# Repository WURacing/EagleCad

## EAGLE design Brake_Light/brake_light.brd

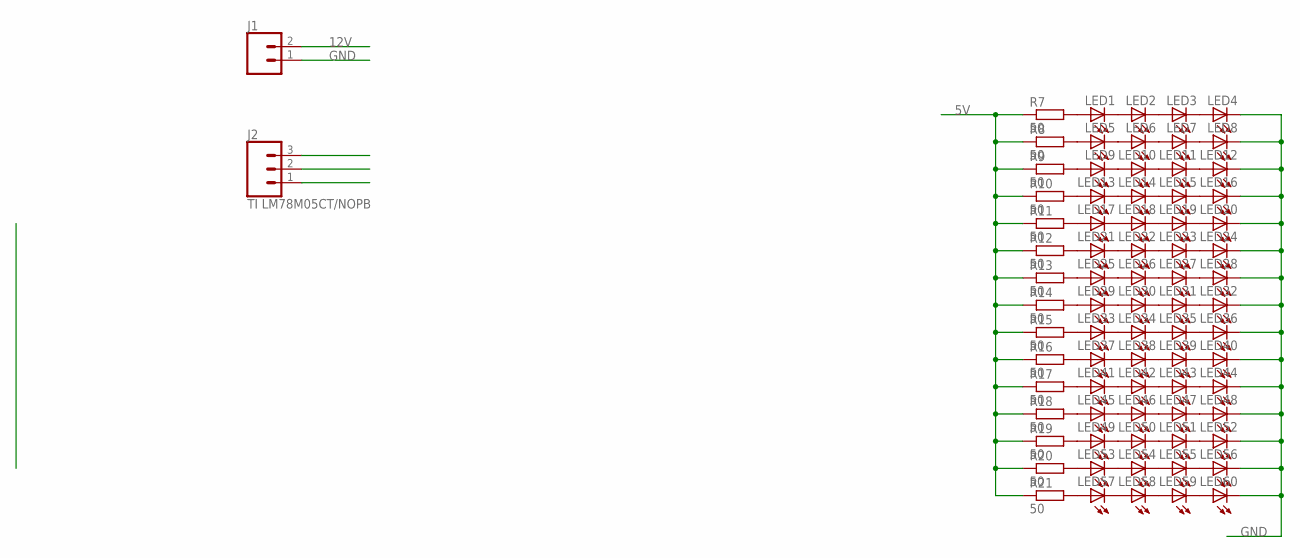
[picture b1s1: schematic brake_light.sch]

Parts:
J1: CONN_02; 1X02
J2: TI LM78M05CT/NOPB; 1X03
LED1, LED2, LED3, LED4, LED5, LED6, LED7, LED8, LED9, LED10, LED11, LED12, LED13, LED14, LED15, LED16, LED17, LED18, LED19, LED20, LED21, LED22, LED23, LED24, LED25, LED26, LED27, LED28, LED29, LED30, LED31, LED32, LED33, LED34, LED35, LED36, LED37, LED38, LED39, LED40, LED41, LED42, LED43, LED44, LED45, LED46, LED47, LED48, LED49, LED50, LED51, LED52, LED53, LED54, LED55, LED56, LED57, LED58, LED59, LED60: LED5MM
R7, R8, R9, R10, R11, R12, R13, R14, R15, R16, R17, R18, R19, R20, R21: 50; R1206

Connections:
5V: J2.3, R7.1, R8.1, R9.1, R10.1, R11.1, R12.1, R13.1, R14.1, R15.1, R16.1, R17.1, R18.1, R19.1, R20.1, R21.1
12V: J1.2, J2.1
GND: J1.1, J2.2, LED4.K (C), LED8.K (C), LED12.K (C), LED16.K (C), LED20.K (C), LED24.K (C), LED28.K (C), LED32.K (C), LED36.K (C), LED40.K (C), LED44.K (C), LED48.K (C), LED52.K (C), LED56.K (C), LED60.K (C)
unnamed: LED1.A, R7.2
unnamed: LED1.K (C), LED2.A
unnamed: LED2.K (C), LED3.A
unnamed: LED3.K (C), LED4.A
unnamed: LED5.A, R8.2
unnamed: LED5.K (C), LED6.A
unnamed: LED6.K (C), LED7.A
unnamed: LED7.K (C), LED8.A
unnamed: LED9.A, R9.2
unnamed: LED9.K (C), LED10.A
unnamed: LED10.K (C), LED11.A
unnamed: LED11.K (C), LED12.A
unnamed: LED13.A, R10.2
unnamed: LED13.K (C), LED14.A
unnamed: LED14.K (C), LED15.A
unnamed: LED15.K (C), LED16.A
unnamed: LED17.A, R11.2
unnamed: LED17.K (C), LED18.A
unnamed: LED18.K (C), LED19.A
unnamed: LED19.K (C), LED20.A
unnamed: LED21.A, R12.2
unnamed: LED21.K (C), LED22.A
unnamed: LED22.K (C), LED23.A
unnamed: LED23.K (C), LED24.A
unnamed: LED25.A, R13.2
unnamed: LED25.K (C), LED26.A
unnamed: LED26.K (C), LED27.A
unnamed: LED27.K (C), LED28.A
unnamed: LED29.A, R14.2
unnamed: LED29.K (C), LED30.A
unnamed: LED30.K (C), LED31.A
unnamed: LED31.K (C), LED32.A
unnamed: LED33.A, R15.2
unnamed: LED33.K (C), LED34.A
unnamed: LED34.K (C), LED35.A
unnamed: LED35.K (C), LED36.A
unnamed: LED37.A, R16.2
unnamed: LED37.K (C), LED38.A
unnamed: LED38.K (C), LED39.A
unnamed: LED39.K (C), LED40.A
unnamed: LED41.A, R17.2
unnamed: LED41.K (C), LED42.A
unnamed: LED42.K (C), LED43.A
unnamed: LED43.K (C), LED44.A
unnamed: LED45.A, R18.2
unnamed: LED45.K (C), LED46.A
unnamed: LED46.K (C), LED47.A
unnamed: LED47.K (C), LED48.A
unnamed: LED49.A, R19.2
unnamed: LED49.K (C), LED50.A
unnamed: LED50.K (C), LED51.A
unnamed: LED51.K (C), LED52.A
unnamed: LED53.A, R20.2
unnamed: LED53.K (C), LED54.A
unnamed: LED54.K (C), LED55.A
unnamed: LED55.K (C), LED56.A
unnamed: LED57.A, R21.2
unnamed: LED57.K (C), LED58.A
unnamed: LED58.K (C), LED59.A
unnamed: LED59.K (C), LED60.A

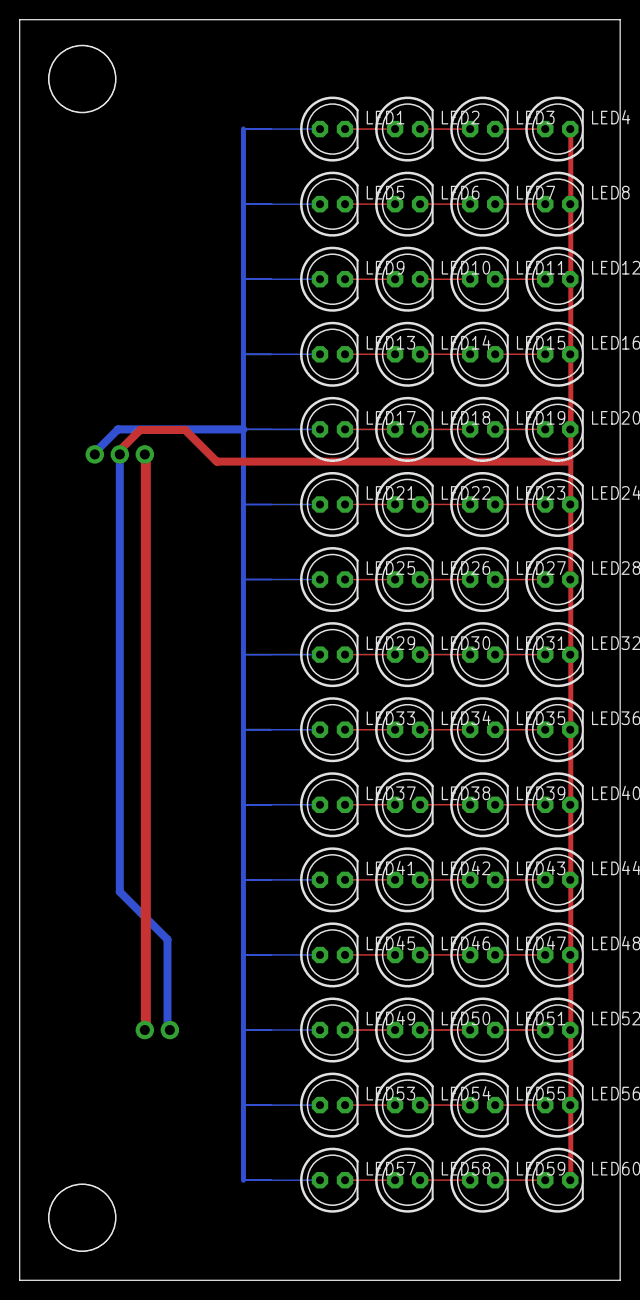
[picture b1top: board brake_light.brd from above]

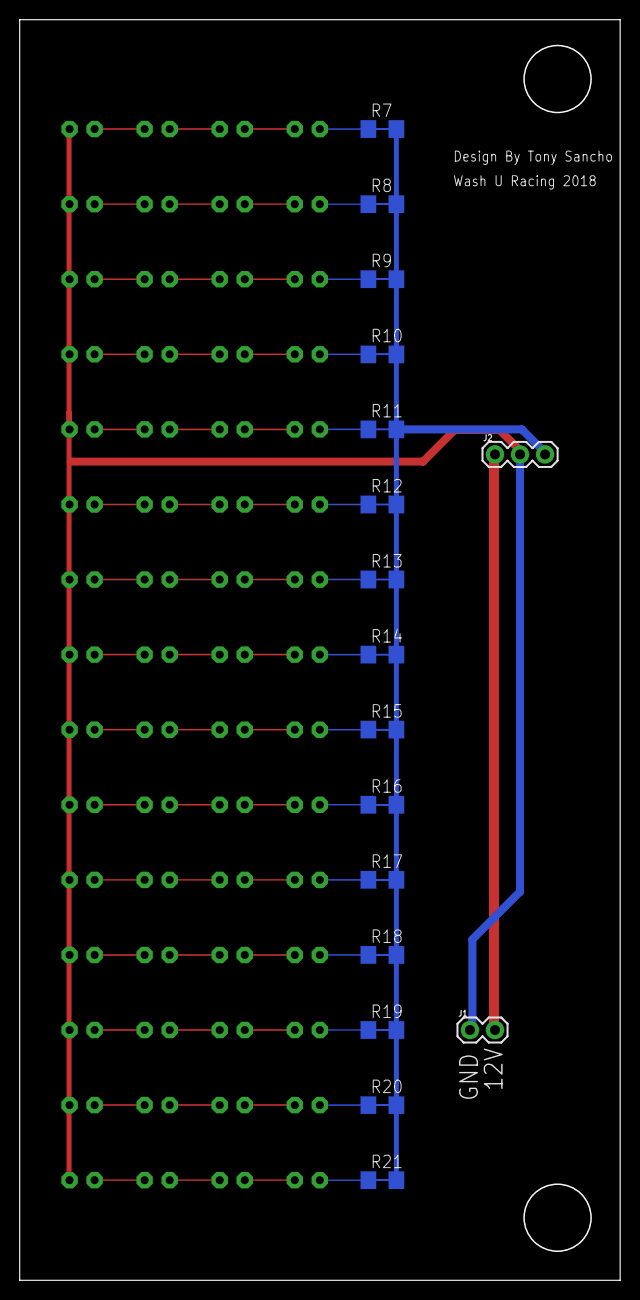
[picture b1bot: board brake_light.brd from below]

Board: 2 copper layers, 60.9 x 127.9 mm, 77 parts (17 on the bottom side), 63 nets.

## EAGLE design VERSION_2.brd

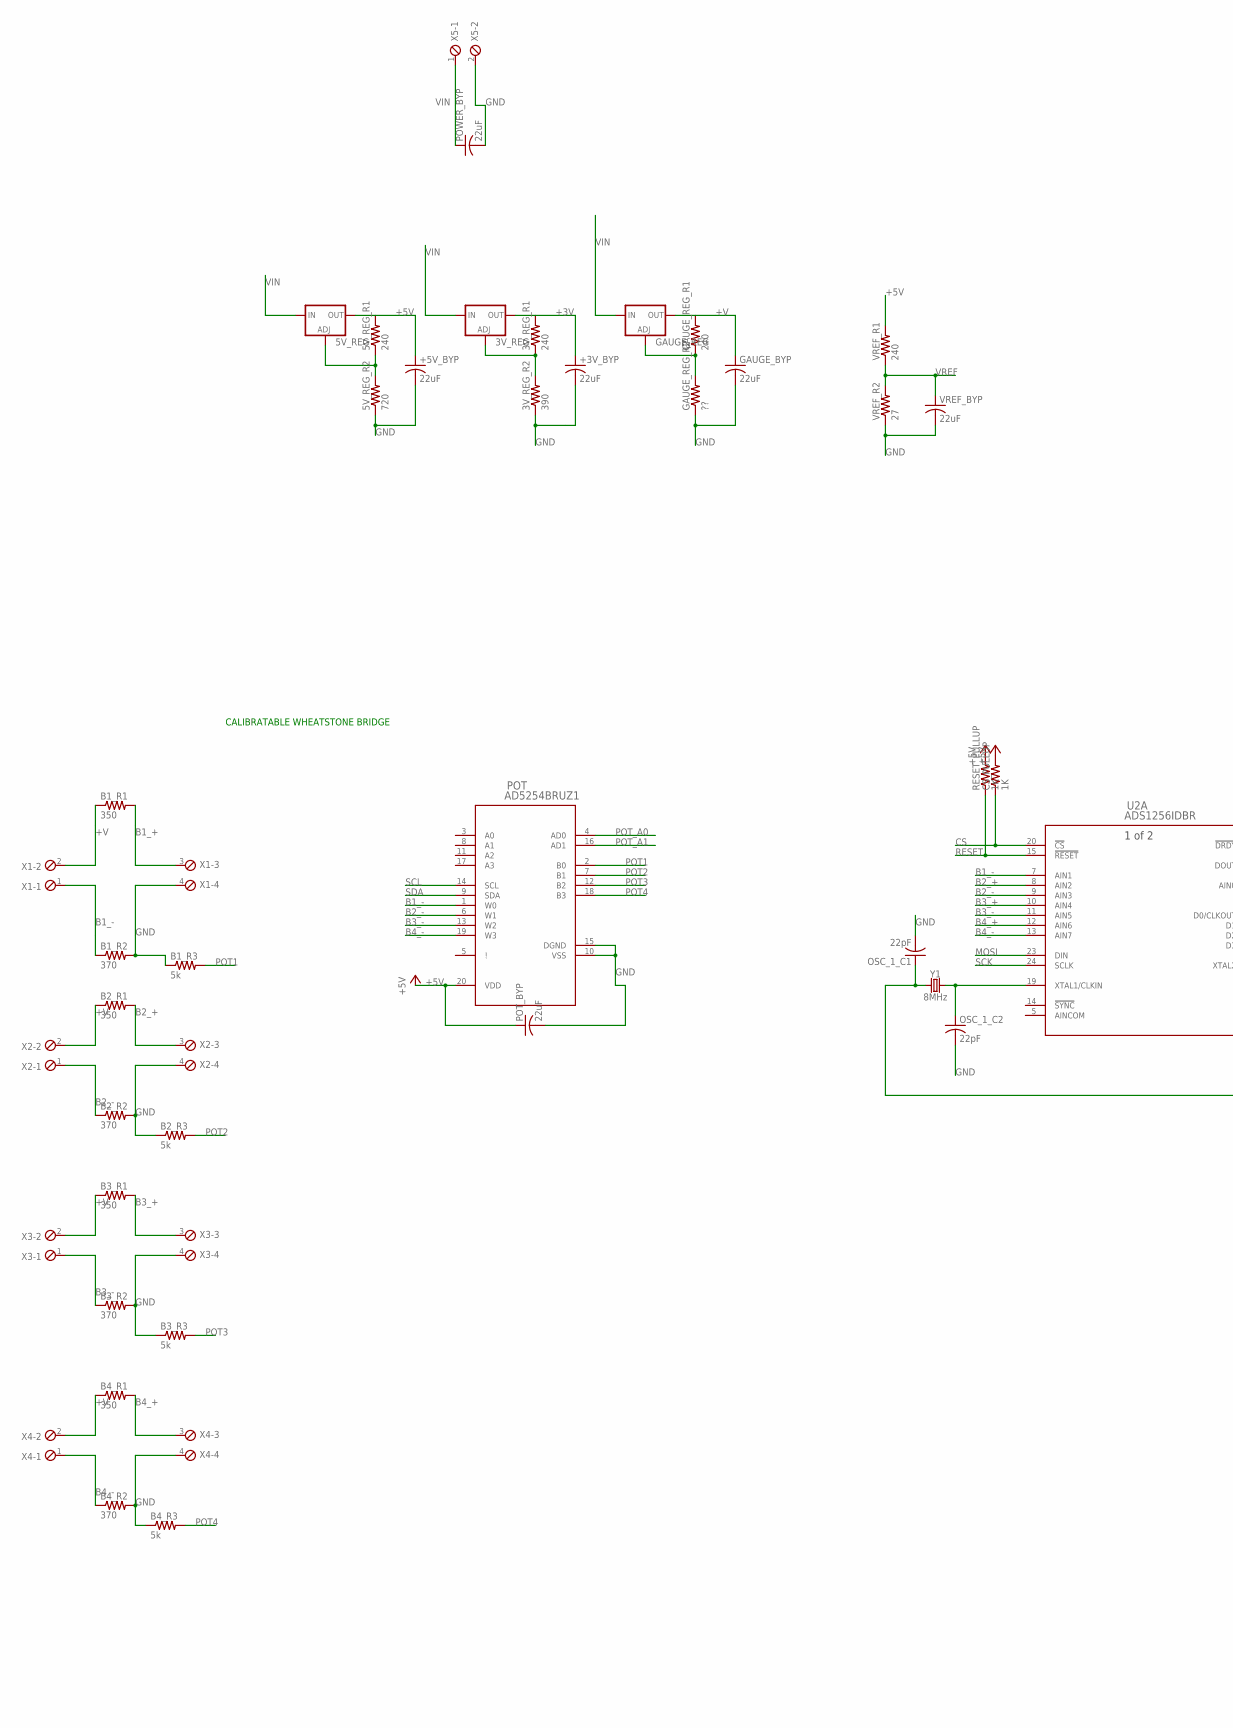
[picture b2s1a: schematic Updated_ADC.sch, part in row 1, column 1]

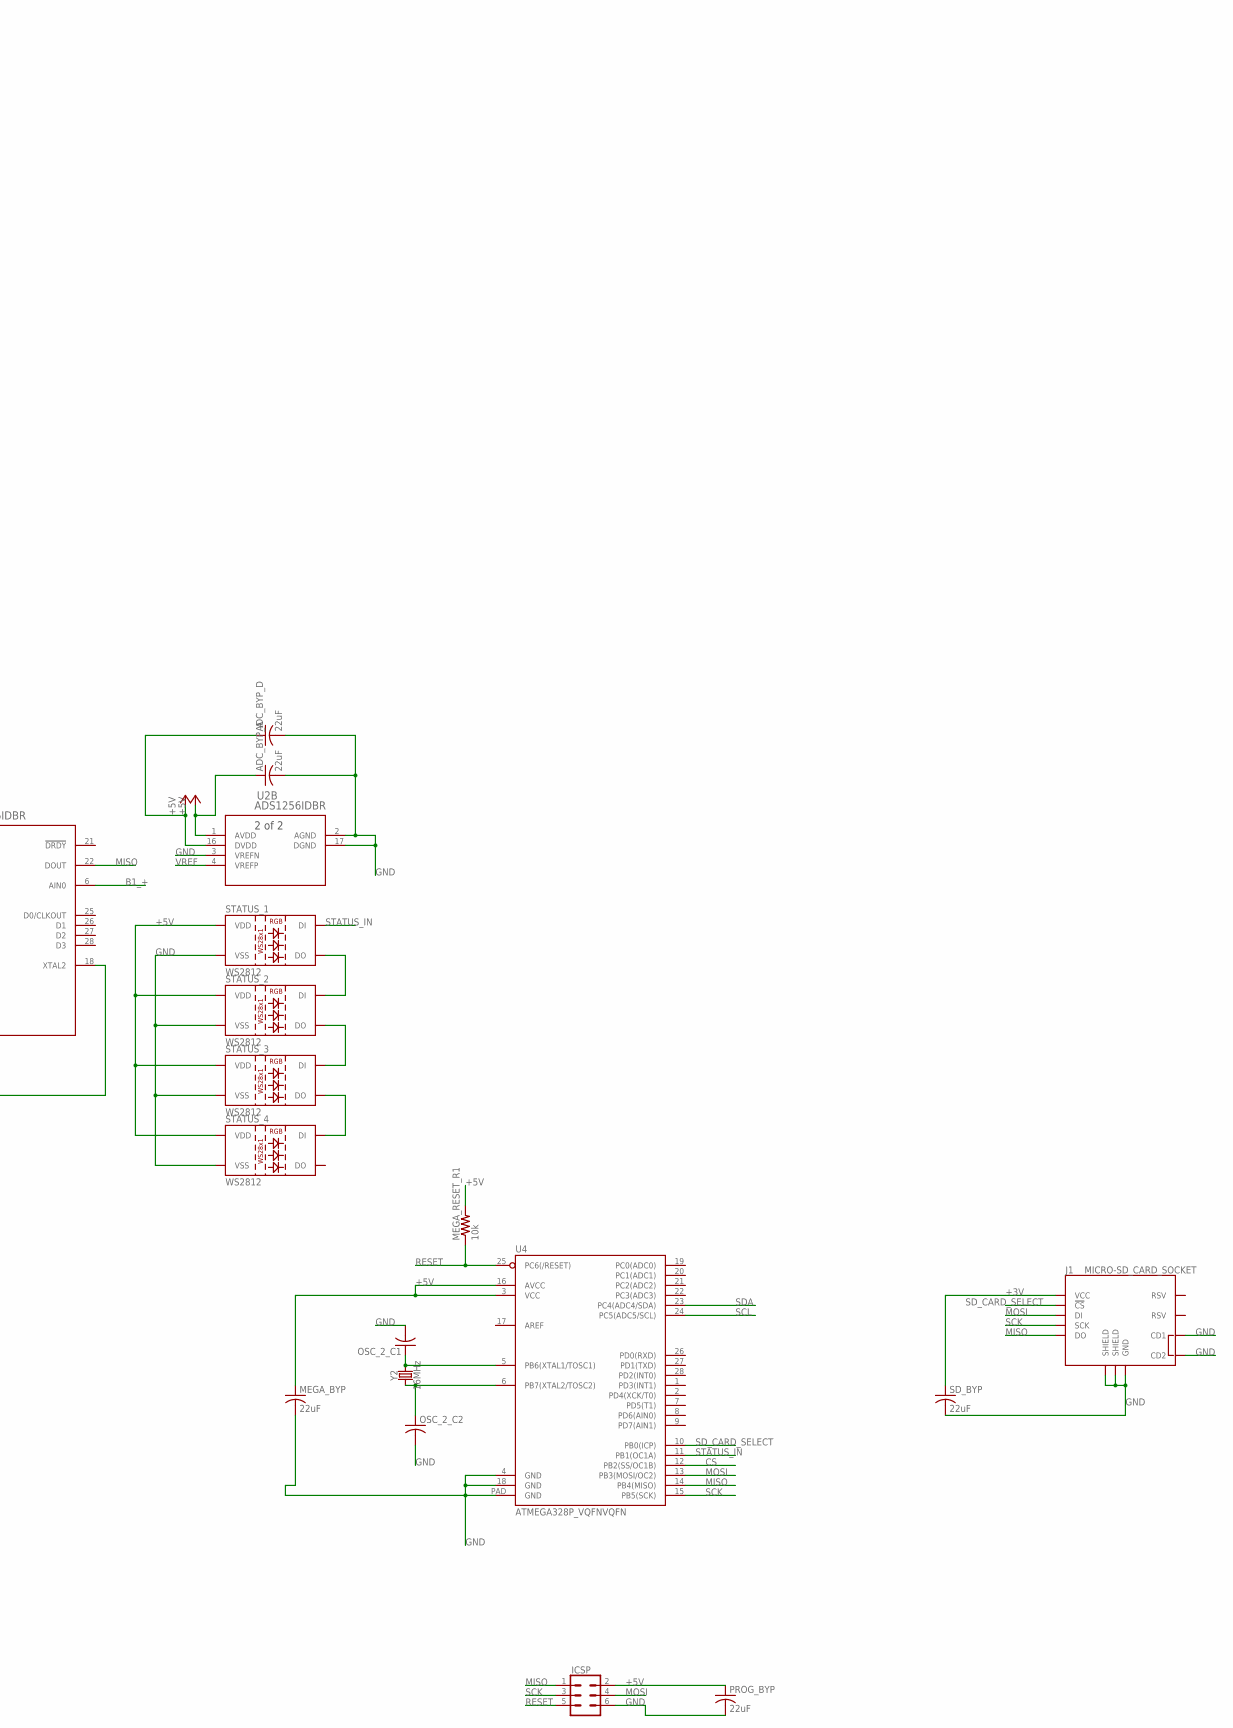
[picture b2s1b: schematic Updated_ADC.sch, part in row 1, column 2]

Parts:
3V_REG, 5V_REG: V_REG_317SMD; SOT223
3V_REG_R1, 5V_REG_R1: 240; R1206
3V_REG_R2: 390; R1206
5V_REG_R2: 720; R1206
+3V_BYP, +5V_BYP: 22uF; C1206
ADC_BYP_A: 22uF; C1206
ADC_BYP_D: 22uF; C1206
B1_R1, B2_R1, B3_R1, B4_R1: 350; R1206
B1_R2, B2_R2, B3_R2, B4_R2: 370; R1206
B1_R3, B2_R3, B3_R3, B4_R3: 5k; R1206
CS_PULLUP: 1K; M1206
GAUGE_BYP: 22uF; C1206
GAUGE_REG: V_REG_317SMD; SOT223
GAUGE_REG_R1: 240; R1206
GAUGE_REG_R2: ??; R1206
ICSP: CONN_03X2FEMALE; 2X3
J1: MICRO-SD_CARD_SOCKET; MICRO-SD-SOCKET
MEGA_BYP: 22uF; C1206
MEGA_RESET_R1: 10k; M1206
OSC_1_C1, OSC_1_C2: 22pF; C1206
OSC_2_C1, OSC_2_C2: C-USC1206; C1206
POT: AD5254BRUZ1; RU_20
POT_BYP: 22uF; C1206
POWER_BYP: 22uF; C1206
PROG_BYP: 22uF; C1206
RESET_PULLUP: 1K; M1206
SD_BYP: 22uF; C1206
STATUS_1, STATUS_2, STATUS_3, STATUS_4: WS2812; LED-TRICOLOR-5050-IC
U2: ADS1256IDBR; DB28
U4: ATMEGA328P_VQFNVQFN; VQFN-28
VREF_BYP: 22uF; C1206
VREF_R1: 240; R1206
VREF_R2: 27; R1206
X1, X2, X3, X4: MPT4; 4POL254
X5: MPT2; 2POL254
Y1: 8MHz; CRYSTAL-SMD-5X3.2-4PAD
Y2: 16MHz; CRYSTAL-SMD-5X3.2-4PAD

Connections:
+3V: 3V_REG.2 (OUT), 3V_REG_R1.2, +3V_BYP.1, J1.VCC, SD_BYP.1
+5V: 5V_REG.2 (OUT), 5V_REG_R1.2, +5V_BYP.1, ADC_BYP_A.1, ADC_BYP_D.1, CS_PULLUP.2, ICSP.2, MEGA_BYP.1, MEGA_RESET_R1.2, POT.20 (VDD), POT_BYP.1, PROG_BYP.1, RESET_PULLUP.2, STATUS_1.3 (VDD), STATUS_1.5 (VDD), STATUS_2.3 (VDD), STATUS_2.5 (VDD), STATUS_3.3 (VDD), STATUS_3.5 (VDD), STATUS_4.3 (VDD), STATUS_4.5 (VDD), U2.1 (AVDD), U2.16 (DVDD), U4.3 (VCC), U4.16 (AVCC), VREF_R1.2; also elsewhere on the board
+V: B1_R1.1, B2_R1.1, B3_R1.1, B4_R1.1, GAUGE_BYP.1, GAUGE_REG.2 (OUT), GAUGE_REG_R1.2, X1.2, X2.2, X3.2, X4.2
B1_+: B1_R1.2, U2.6 (AIN0), X1.3; also elsewhere on the board
B1_-: B1_R2.1, POT.1 (W0), U2.7 (AIN1), X1.1; also elsewhere on the board
B2_+: B2_R1.2, U2.8 (AIN2), X2.3; also elsewhere on the board
B2_-: B2_R2.1, POT.6 (W1), U2.9 (AIN3), X2.1; also elsewhere on the board
B3_+: B3_R1.2, U2.10 (AIN4), X3.3; also elsewhere on the board
B3_-: B3_R2.1, POT.13 (W2), U2.11 (AIN5), X3.1; also elsewhere on the board
B4_+: B4_R1.2, U2.12 (AIN6), X4.3; also elsewhere on the board
B4_-: B4_R2.1, POT.19 (W3), U2.13 (AIN7), X4.1; also elsewhere on the board
CS: CS_PULLUP.1, U2.20 (!CS), U4.12 (PB2(SS/OC1B)); also elsewhere on the board
GND: 3V_REG_R2.1, 5V_REG_R2.1, +3V_BYP.2, +5V_BYP.2, ADC_BYP_A.2, ADC_BYP_D.2, B1_R2.2, B1_R3.1, B2_R2.2, B2_R3.1, B3_R2.2, B3_R3.1, B4_R2.2, B4_R3.1, GAUGE_BYP.2, GAUGE_REG_R2.1, ICSP.6, J1.CD1, J1.CD2, J1.GND, J1.GND1 (SHIELD), J1.GND3 (SHIELD), MEGA_BYP.2, OSC_1_C1.2, OSC_1_C2.2, OSC_2_C1.2, OSC_2_C2.2, POT.10 (VSS), POT.15 (DGND), POT_BYP.2, POWER_BYP.2, PROG_BYP.2, SD_BYP.2, STATUS_1.6 (VSS), STATUS_2.6 (VSS), STATUS_3.6 (VSS), STATUS_4.6 (VSS), U2.2 (AGND), U2.3 (VREFN), U2.17 (DGND), U4.4 (GND), U4.18 (GND), U4.PAD (GND), VREF_BYP.2, VREF_R2.1, X1.4, X2.4, X3.4, X4.4, X5.2; also elsewhere on the board
MISO: ICSP.1, J1.DO, U2.22 (DOUT), U4.14 (PB4(MISO)); also elsewhere on the board
MOSI: ICSP.4, J1.DI, U2.23 (DIN), U4.13 (PB3(MOSI/OC2)); also elsewhere on the board
unnamed 15: OSC_1_C2.1, U2.19 (XTAL1/CLKIN), Y1.3 (2); also elsewhere on the board
unnamed 16: OSC_1_C1.1, U2.18 (XTAL2), Y1.1; also elsewhere on the board
unnamed 17: OSC_2_C1.1, U4.5 (PB6(XTAL1/TOSC1)), Y2.3 (2); also elsewhere on the board
unnamed 18: OSC_2_C2.1, U4.6 (PB7(XTAL2/TOSC2)), Y2.1; also elsewhere on the board
unnamed: 5V_REG.1 (ADJ), 5V_REG_R1.1, 5V_REG_R2.2
unnamed: 3V_REG.1 (ADJ), 3V_REG_R1.1, 3V_REG_R2.2
unnamed: STATUS_1.1 (DO), STATUS_2.2 (DI)
unnamed: STATUS_2.1 (DO), STATUS_3.2 (DI)
unnamed: STATUS_3.1 (DO), STATUS_4.2 (DI)
unnamed: GAUGE_REG.1 (ADJ), GAUGE_REG_R1.1, GAUGE_REG_R2.2
POT1: B1_R3.2, POT.2 (B0)
POT2: B2_R3.2, POT.7 (B1)
POT3: B3_R3.2, POT.12 (B2)
POT4: B4_R3.2, POT.18 (B3)
POT_A0: POT.4 (AD0); also elsewhere on the board
POT_A1: POT.16 (AD1); also elsewhere on the board
RESET: ICSP.5, MEGA_RESET_R1.1, RESET_PULLUP.1, U2.15 (!RESET), U4.25 (PC6(/RESET)); also elsewhere on the board
SCK: ICSP.3, J1.SCLK (SCK), U2.24 (SCLK), U4.15 (PB5(SCK)); also elsewhere on the board
SCL: POT.14 (SCL), U4.24 (PC5(ADC5/SCL)); also elsewhere on the board
SDA: POT.9 (SDA), U4.23 (PC4(ADC4/SDA)); also elsewhere on the board
SD_CARD_SELECT: J1.CS (!CS), U4.10 (PB0(ICP)); also elsewhere on the board
STATUS_IN: STATUS_1.2 (DI), U4.11 (PB1(OC1A)); also elsewhere on the board
VIN: 3V_REG.3 (IN), 5V_REG.3 (IN), GAUGE_REG.3 (IN), POWER_BYP.1, X5.1
VREF: U2.4 (VREFP), VREF_BYP.1, VREF_R1.1, VREF_R2.2; also elsewhere on the board

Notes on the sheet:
CALIBRATABLE WHEATSTONE BRIDGE

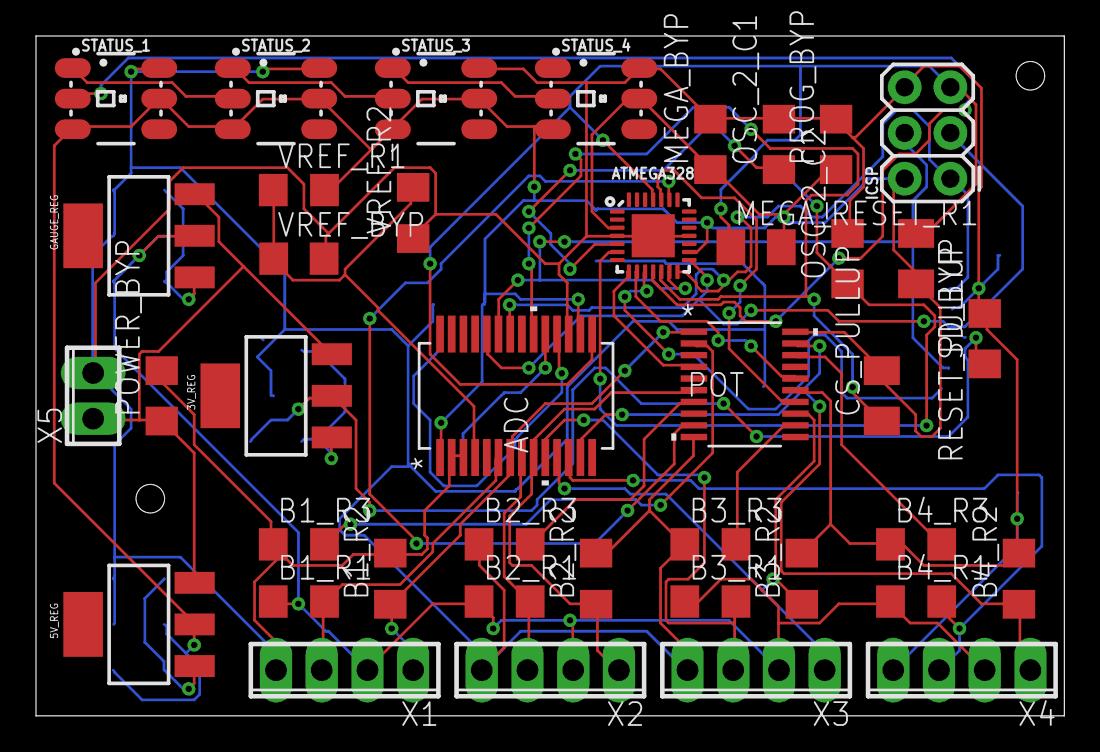
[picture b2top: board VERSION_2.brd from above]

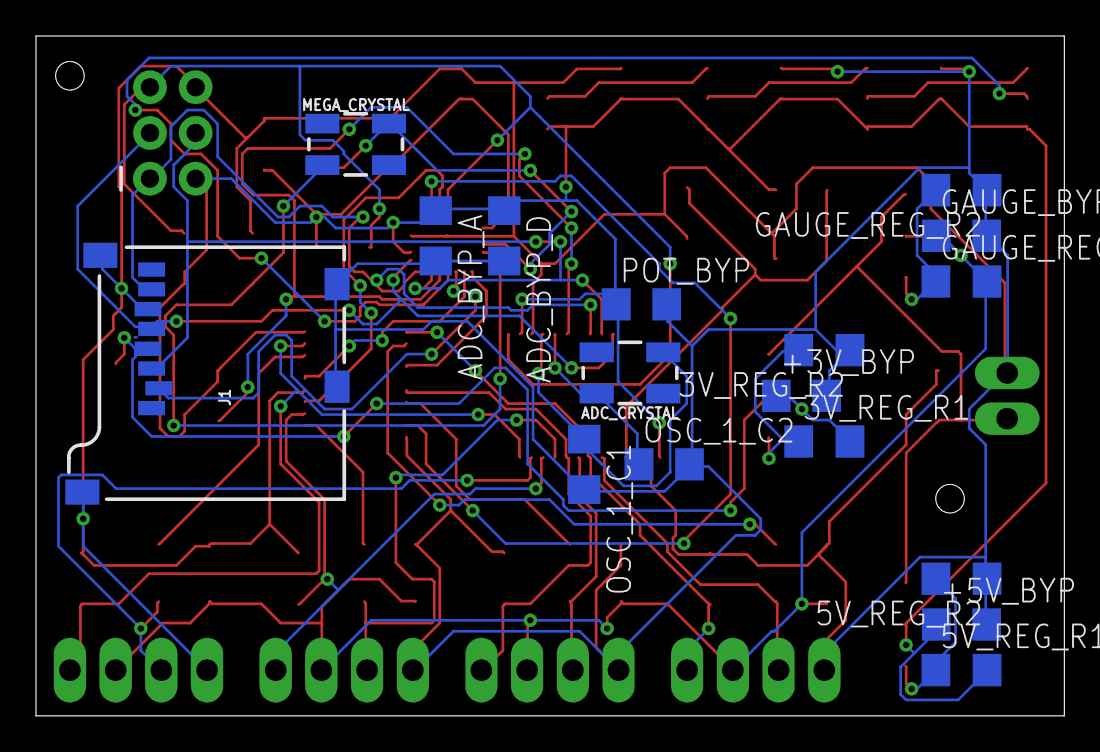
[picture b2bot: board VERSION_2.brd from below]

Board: 2 copper layers, 57.1 x 37.8 mm, 57 parts (17 on the bottom side), 39 nets.

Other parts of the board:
ADC: ADS1256IDBR; DB28
ADC_CRYSTAL: 8MHz; CRYSTAL-SMD-5X3.2-4PAD
ATMEGA328: ATMEGA328P_VQFNVQFN; VQFN-28
MEGA_CRYSTAL: 16MHz; CRYSTAL-SMD-5X3.2-4PAD

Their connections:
+5V: ADC.1, ADC.16, ATMEGA328.3, ATMEGA328.16; also elsewhere on the board
B1_+: ADC.6; also elsewhere on the board
B1_-: ADC.7; also elsewhere on the board
B2_+: ADC.8; also elsewhere on the board
B2_-: ADC.9; also elsewhere on the board
B3_+: ADC.10; also elsewhere on the board
B3_-: ADC.11; also elsewhere on the board
B4_+: ADC.12; also elsewhere on the board
B4_-: ADC.13; also elsewhere on the board
CS: ADC.20, ATMEGA328.12; also elsewhere on the board
GND: ADC.2, ADC.3, ADC.17, ATMEGA328.4, ATMEGA328.18, ATMEGA328.PAD; also elsewhere on the board
MISO: ADC.22, ATMEGA328.14; also elsewhere on the board
MOSI: ADC.23, ATMEGA328.13; also elsewhere on the board
unnamed 15: ADC.19, ADC_CRYSTAL.3; also elsewhere on the board
unnamed 16: ADC.18, ADC_CRYSTAL.1; also elsewhere on the board
unnamed 17: ATMEGA328.5, MEGA_CRYSTAL.3; also elsewhere on the board
unnamed 18: ATMEGA328.6, MEGA_CRYSTAL.1; also elsewhere on the board
POT_A0: ATMEGA328.8; also elsewhere on the board
POT_A1: ATMEGA328.9; also elsewhere on the board
RESET: ADC.15, ATMEGA328.25; also elsewhere on the board
SCK: ADC.24, ATMEGA328.15; also elsewhere on the board
SCL: ATMEGA328.24; also elsewhere on the board
SDA: ATMEGA328.23; also elsewhere on the board
SD_CARD_SELECT: ATMEGA328.10; also elsewhere on the board
STATUS_IN: ATMEGA328.11; also elsewhere on the board
VREF: ADC.4; also elsewhere on the board

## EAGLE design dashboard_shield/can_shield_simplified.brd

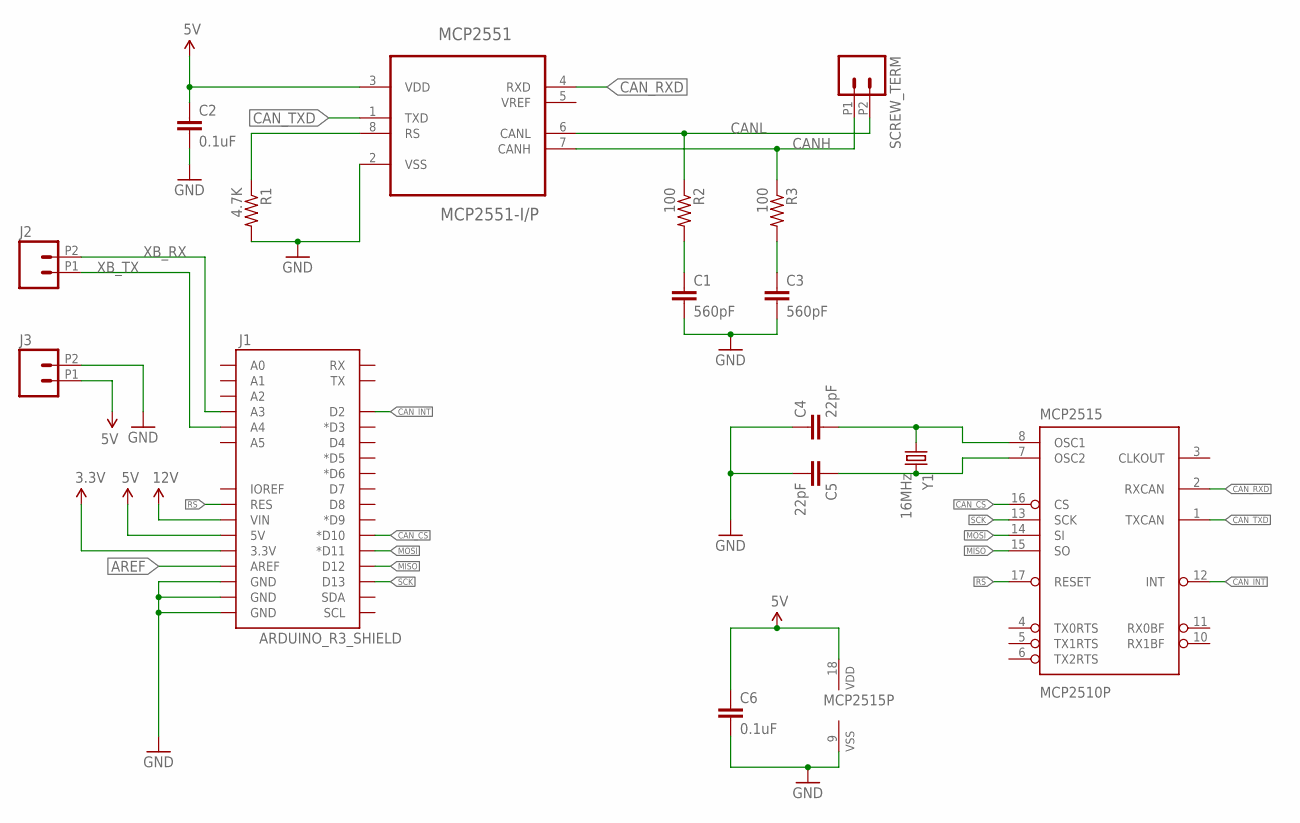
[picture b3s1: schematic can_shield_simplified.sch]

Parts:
C1, C3: 560pF; CAP-PTH-SMALL
C2, C6: 0.1uF; CAP-PTH-SMALL
C4, C5: 22pF; CAP-PTH-SMALL
J1: ARDUINO_R3_SHIELD; UNO_R3_SHIELD
J2, J3: M022.54MM_SCREWTERM; 1X02_2.54_SCREWTERM
MCP2515: MCP2510P; DIL18
MCP2551: MCP2551-I/P; DIP254P762X432-8
R1: 4.7K; AXIAL-0.3
R2, R3: 100; AXIAL-0.3
SCREW_TERM: M022.54MM_SCREWTERM; 1X02_2.54_SCREWTERM
Y1: 16MHz; HC49US

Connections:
3.3V: J1.3.3V
5V: C2.1, C6.1, J1.5V, J3.P1 (1), MCP2515.18 (VDD), MCP2551.3 (VDD)
12V: J1.VIN
AREF: J1.AREF
CANH: MCP2551.7 (CANH), R3.P$1 (1), SCREW_TERM.P1 (1)
CANH_CAP: C3.1, R3.P$2 (2)
CANL: MCP2551.6 (CANL), R2.P$1 (1), SCREW_TERM.P2 (2)
CANL_CAP: C1.1, R2.P$2 (2)
CAN_CS: J1.D10 (*D10), MCP2515.16 (CS)
CAN_INT: J1.D2, MCP2515.12 (INT)
CAN_RXD: MCP2515.2 (RXCAN), MCP2551.4 (RXD)
CAN_TXD: MCP2515.1 (TXCAN), MCP2551.1 (TXD)
GND: C1.2, C2.2, C3.2, C4.1, C5.2, C6.2, J1.GND@0 (GND), J1.GND@1 (GND), J1.GND@2 (GND), J3.P2 (2), MCP2515.9 (VSS), MCP2551.2 (VSS), R1.P$2 (2)
MISO: J1.D12, MCP2515.15 (SO)
MOSI: J1.D11 (*D11), MCP2515.14 (SI)
unnamed: MCP2551.8 (RS), R1.P$1 (1)
unnamed: C4.2, MCP2515.8 (OSC1), Y1.1
unnamed: C5.1, MCP2515.7 (OSC2), Y1.2
RS: J1.RES, MCP2515.17 (RESET)
SCK: J1.D13, MCP2515.13 (SCK)
XB_RX: J1.A3, J2.P2 (2)
XB_TX: J1.A4, J2.P1 (1)

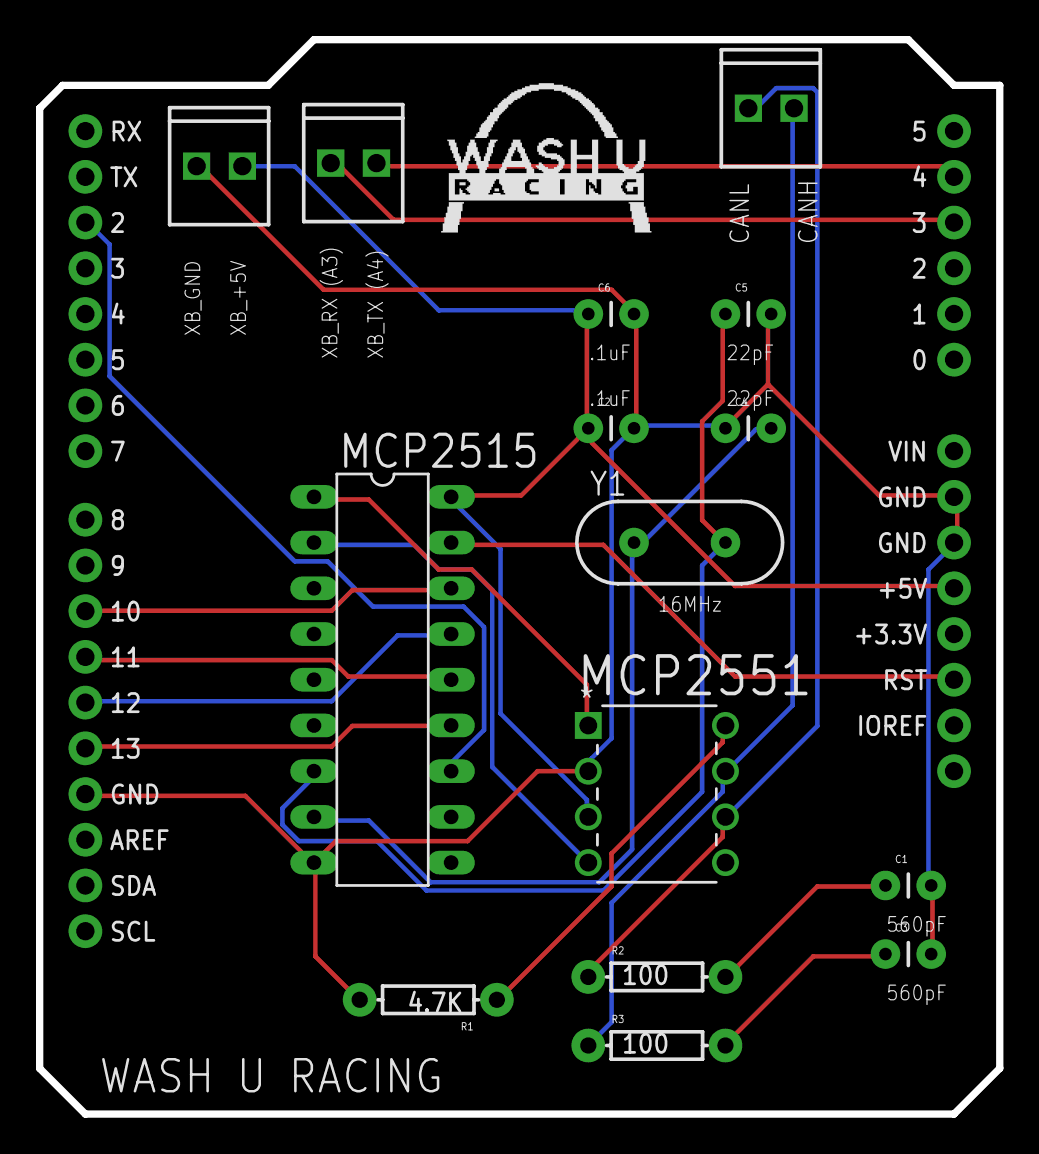
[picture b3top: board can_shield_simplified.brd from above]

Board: 2 copper layers, 53.3 x 59.7 mm, 16 parts (0 on the bottom side), 19 nets.

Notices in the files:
parts and their libraries:
SparkFun-Connectors: Licensing: Creative Commons ShareAlike 4.0 International - https://creativecommons.org/licenses/by-sa/4.0
